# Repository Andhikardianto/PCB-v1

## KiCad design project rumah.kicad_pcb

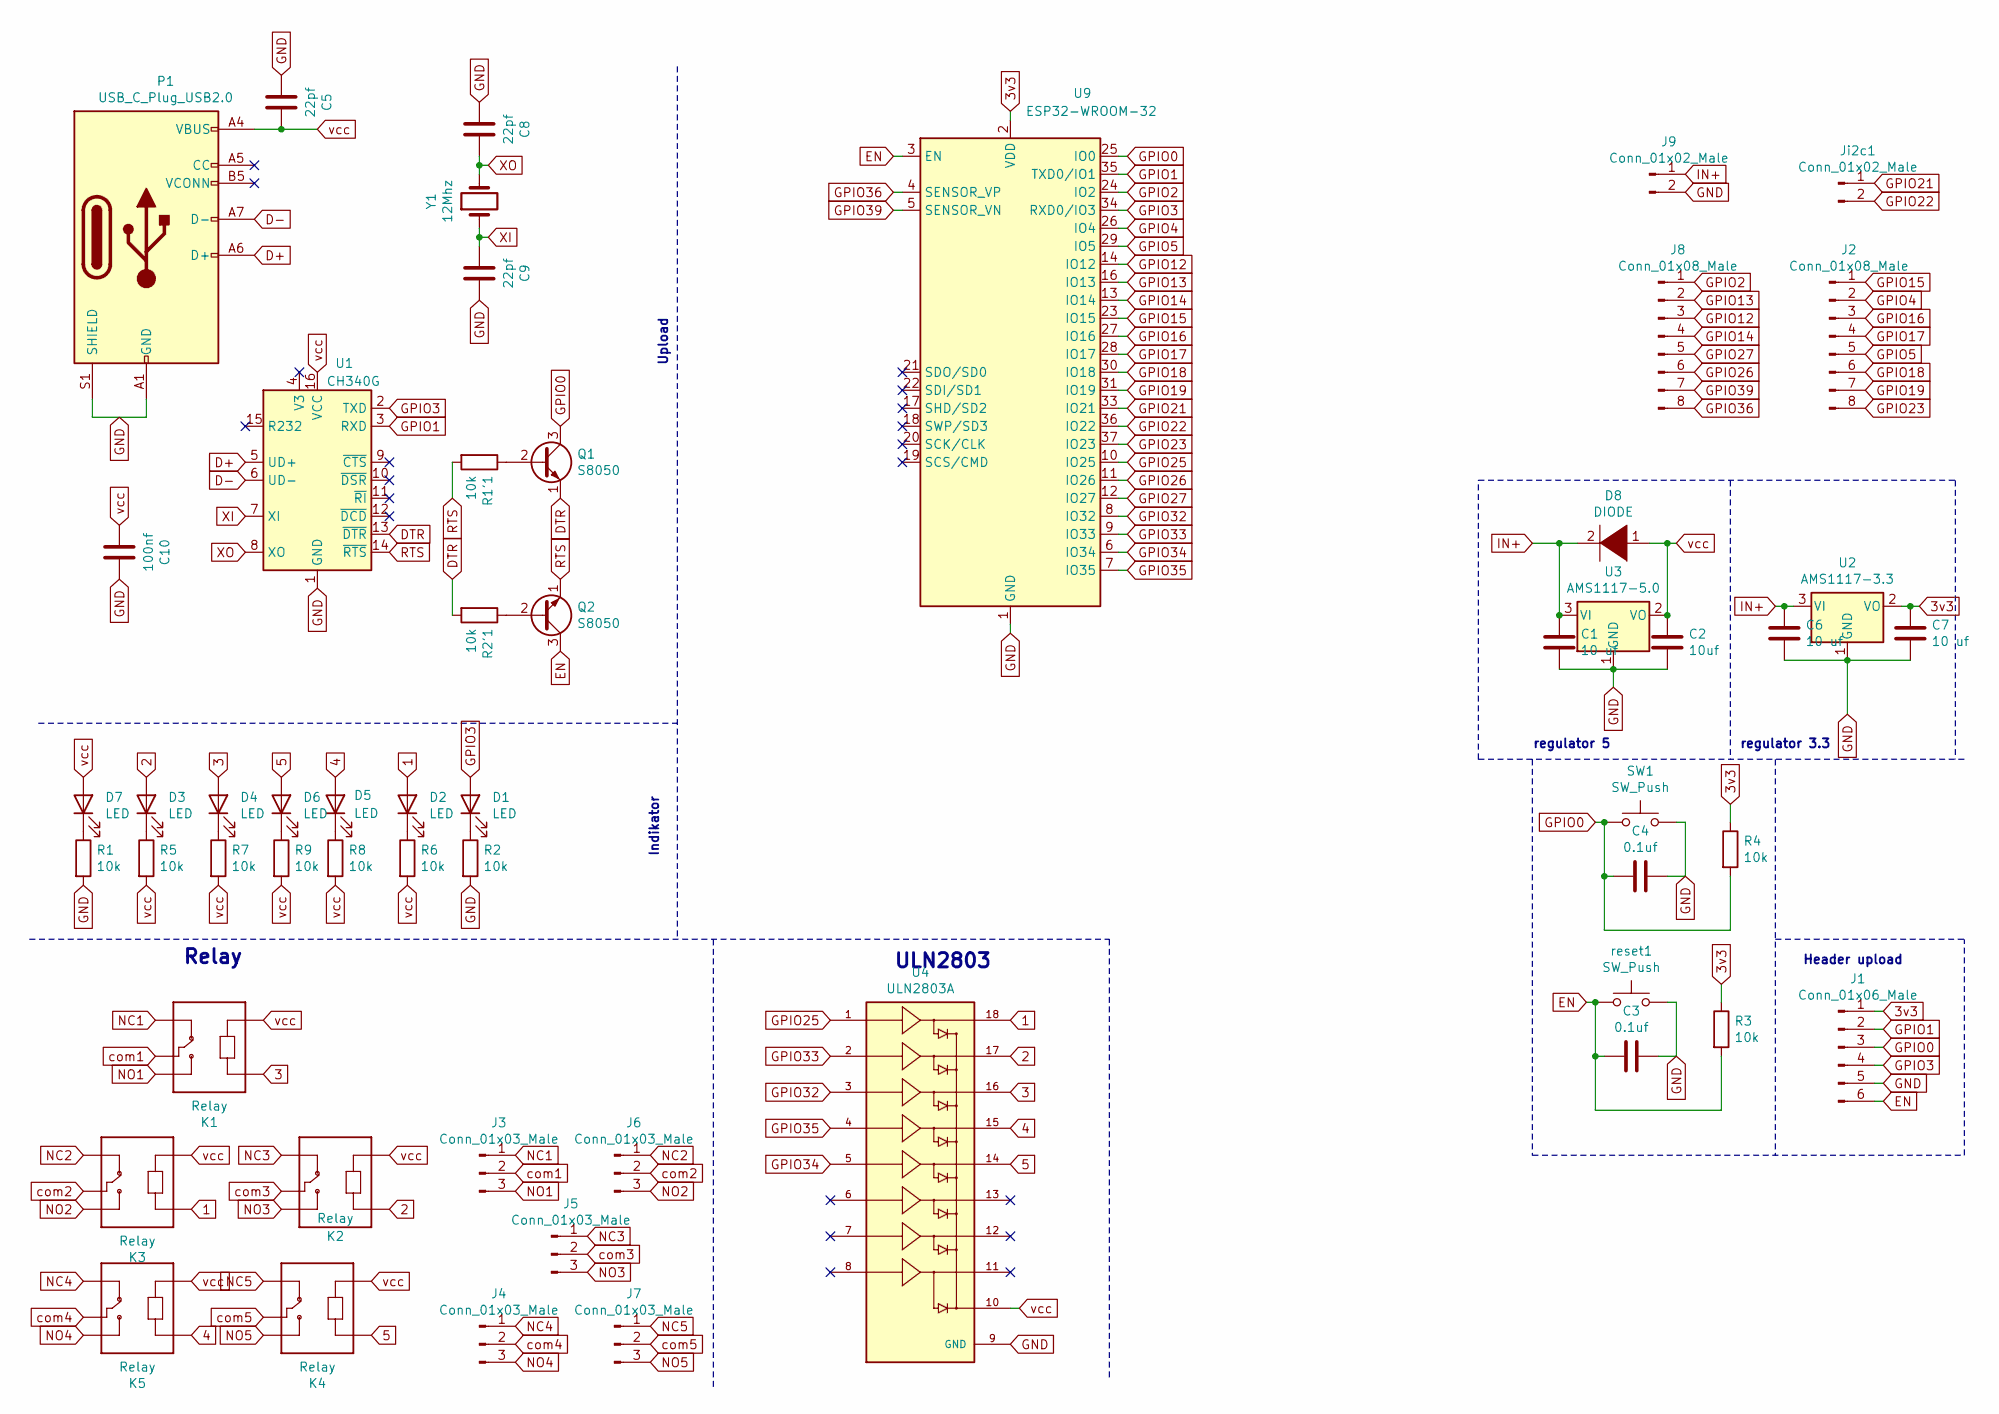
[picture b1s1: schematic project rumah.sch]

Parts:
C1, C6, C7: 10 uf; C_0805_2012Metric_Pad1.18x1.45mm_HandSolder
C2: 10uf; C_0805_2012Metric_Pad1.18x1.45mm_HandSolder
C3, C4: 0.1uf; C_0805_2012Metric_Pad1.18x1.45mm_HandSolder
C5, C8, C9: 22pf; C_0805_2012Metric_Pad1.18x1.45mm_HandSolder
C10: 100nf; C_0805_2012Metric_Pad1.18x1.45mm_HandSolder
D1, D2, D3, D4, D5, D6, D7: LED; LED_D5.0mm
D8: DIODE; D_SMA_Handsoldering
J1: Conn_01x06_Male; PinSocket_2x03_P2.54mm_Vertical
J2, J8: Conn_01x08_Male; PinHeader_1x08_P2.54mm_Vertical
J3, J4, J5, J6, J7: Conn_01x03_Male; TerminalBlock_Altech_AK300-3_P5.00mm
J9: Conn_01x02_Male; TerminalBlock_Altech_AK300-2_P5.00mm
Ji2c1: Conn_01x02_Male; PinHeader_1x02_P2.54mm_Vertical
K1, K2, K3, K4, K5: Relay; RELAY_SRD-05VDC-SL-C
P1: USB_C_Plug_USB2.0; USB_C_Receptacle_XKB_U262-16XN-4BVC11
Q1, Q2: S8050; TO-92_Inline
R1, R1'1, R2, R2'1, R3, R4, R5, R6, R7, R8, R9: 10k; R_0805_2012Metric_Pad1.20x1.40mm_HandSolder
SW1: SW_Push; SW_PUSH_6mm
U1: CH340G; SOIC-16_3.9x9.9mm_P1.27mm
U2: AMS1117-3.3; SOT-223-3_TabPin2
U3: AMS1117-5.0; SOT-223-3_TabPin2
U4: ULN2803A; DIP850W46P254L2324H393Q18; PARTREV 4
U9: ESP32-WROOM-32
Y1: 12Mhz; Crystal_HC51-U_Vertical
reset1: SW_Push; SW_PUSH_6mm

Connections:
1: D2.2 (A), K3.A1, U4.18
2: D3.2 (A), K2.A1, U4.17
3: D4.2 (A), K1.A1, U4.16
3v3: C7.1, J1.1, R3.1, R4.1, U2.2 (VO), U9.2 (VDD)
4: D5.2 (A), K5.A1, U4.15
5: D6.2 (A), K4.A1, U4.14
D+: P1.A6 (D+), U1.5 (UD+)
D-: P1.A7 (D-), U1.6 (UD-)
DTR: Q1.1 (E), R2'1.2, U1.13 (~DTR)
EN: C3.2, J1.6, Q2.3 (C), R3.2, U9.3 (EN), reset1.1
GND: C1.2, C2.2, C3.1, C4.1, C5.2, C6.2, C7.2, C8.2, C9.1, C10.1, J1.5, J9.2, P1.A1 (GND), P1.A12 (GND), P1.B1 (GND), P1.B12 (GND), P1.S1 (SHIELD), R1.2, R2.2, SW1.2, U1.1 (GND), U2.1 (GND), U3.1 (GND), U4.9 (GND), U9.1 (GND), U9.15 (GND), U9.38 (GND), U9.39 (GND), reset1.2
GPIO0: C4.2, J1.3, Q1.3 (C), R4.2, SW1.1, U9.25 (IO0)
GPIO1: J1.2, U1.3 (RXD), U9.35 (TXD0/IO1)
GPIO2: J8.1, U9.24 (IO2)
GPIO3: D1.2 (A), J1.4, U1.2 (TXD), U9.34 (RXD0/IO3)
GPIO4: J2.2, U9.26 (IO4)
GPIO5: J2.5, U9.29 (IO5)
GPIO12: J8.3, U9.14 (IO12)
GPIO13: J8.2, U9.16 (IO13)
GPIO14: J8.4, U9.13 (IO14)
GPIO15: J2.1, U9.23 (IO15)
GPIO16: J2.3, U9.27 (IO16)
GPIO17: J2.4, U9.28 (IO17)
GPIO18: J2.6, U9.30 (IO18)
GPIO19: J2.7, U9.31 (IO19)
GPIO21: Ji2c1.1, U9.33 (IO21)
GPIO22: Ji2c1.2, U9.36 (IO22)
GPIO23: J2.8, U9.37 (IO23)
GPIO25: U4.1, U9.10 (IO25)
GPIO26: J8.6, U9.11 (IO26)
GPIO27: J8.5, U9.12 (IO27)
GPIO32: U4.3, U9.8 (IO32)
GPIO33: U4.2, U9.9 (IO33)
GPIO34: U4.5, U9.6 (IO34)
GPIO35: U4.4, U9.7 (IO35)
GPIO36: J8.8, U9.4 (SENSOR_VP)
GPIO39: J8.7, U9.5 (SENSOR_VN)
IN+: C1.1, C6.1, D8.2 (A), J9.1, U2.3 (VI), U3.3 (VI)
NC1: J3.1, K1.NC
NC2: J6.1, K3.NC
NC3: J5.1, K2.NC
NC4: J4.1, K5.NC
NC5: J7.1, K4.NC
NO1: J3.3, K1.NO
NO2: J6.3, K3.NO
NO3: J5.3, K2.NO
NO4: J4.3, K5.NO
NO5: J7.3, K4.NO
unnamed: D1.1 (K), R2.1
unnamed: D2.1 (K), R6.1
unnamed: D3.1 (K), R5.1
unnamed: D4.1 (K), R7.1
unnamed: D5.1 (K), R8.1
unnamed: D6.1 (K), R9.1
unnamed: D7.1 (K), R1.1
unnamed: Q1.2 (B), R1'1.1
unnamed: Q2.2 (B), R2'1.1
RTS: Q2.1 (E), R1'1.2, U1.14 (~RTS)
XI: C9.2, U1.7 (XI), Y1.1
XO: C8.1, U1.8 (XO), Y1.2
com1: J3.2, K1.COM
com2: J6.2, K3.COM
com3: J5.2, K2.COM
com4: J4.2, K5.COM
com5: J7.2, K4.COM
vcc: C2.1, C5.1, C10.2, D7.2 (A), D8.1 (K), K1.A2, K2.A2, K3.A2, K4.A2, K5.A2, P1.A4 (VBUS), P1.A9 (VBUS), P1.B4 (VBUS), P1.B9 (VBUS), R5.2, R6.2, R7.2, R8.2, R9.2, U1.16 (VCC), U3.2 (VO), U4.10

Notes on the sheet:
regulator 3.3
regulator 5
Relay
ULN2803
Indikator
Upload
Header upload

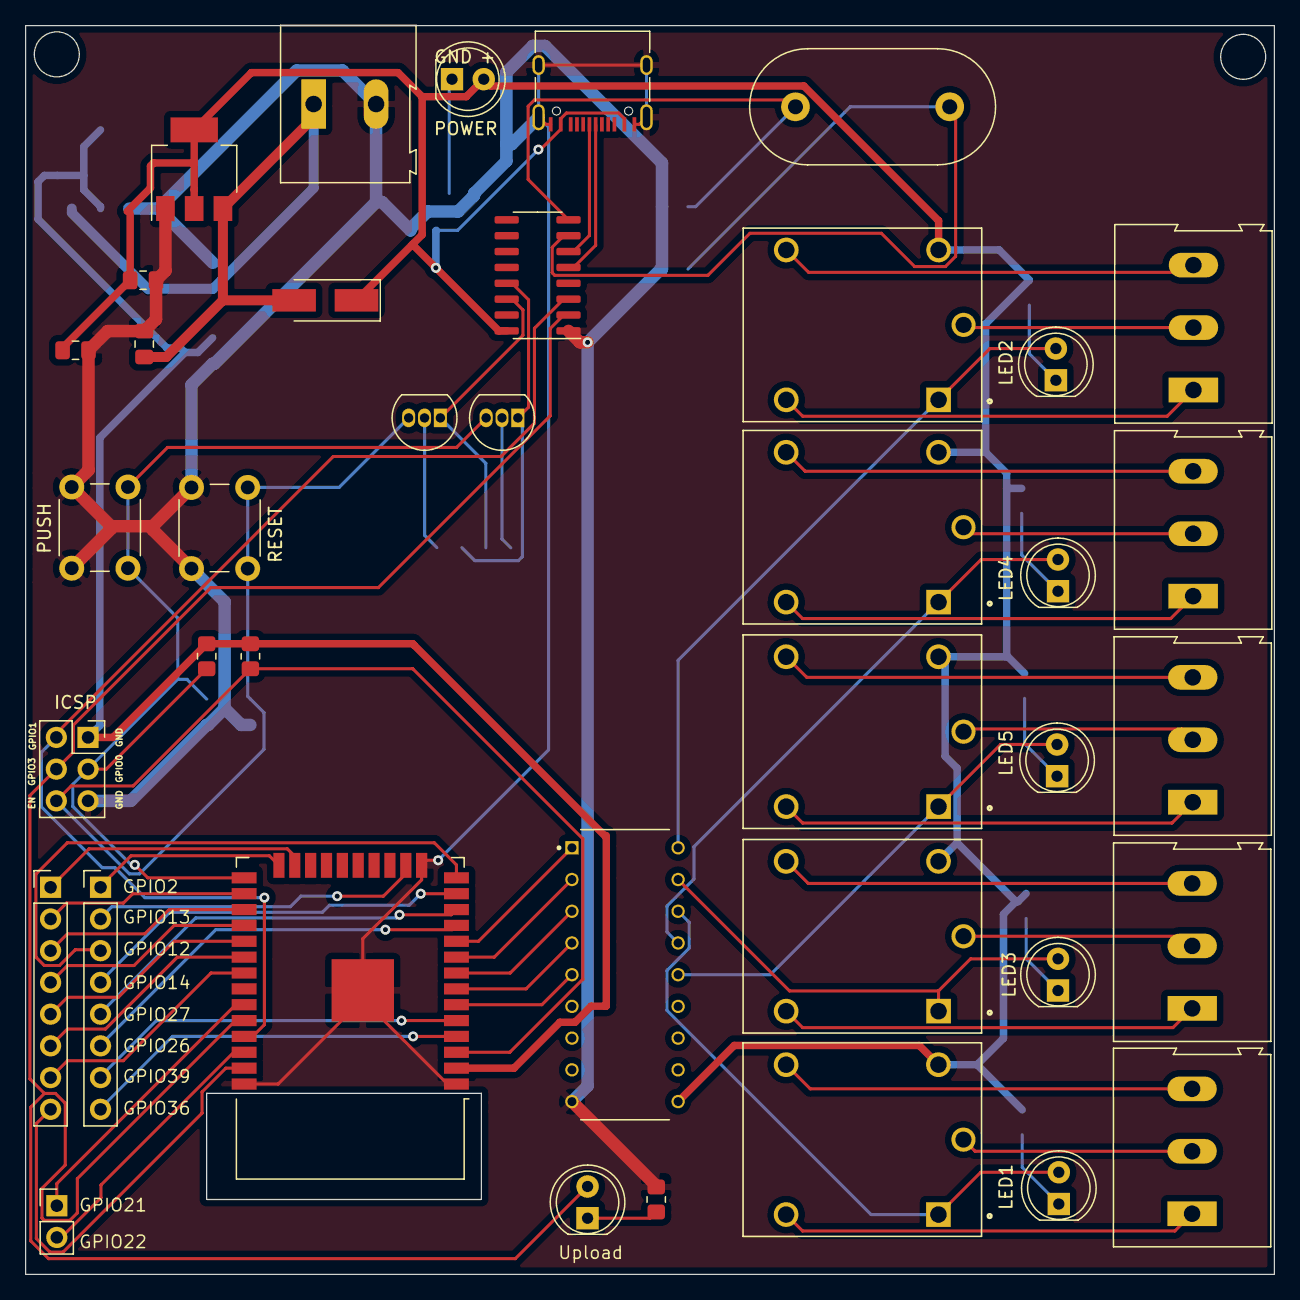
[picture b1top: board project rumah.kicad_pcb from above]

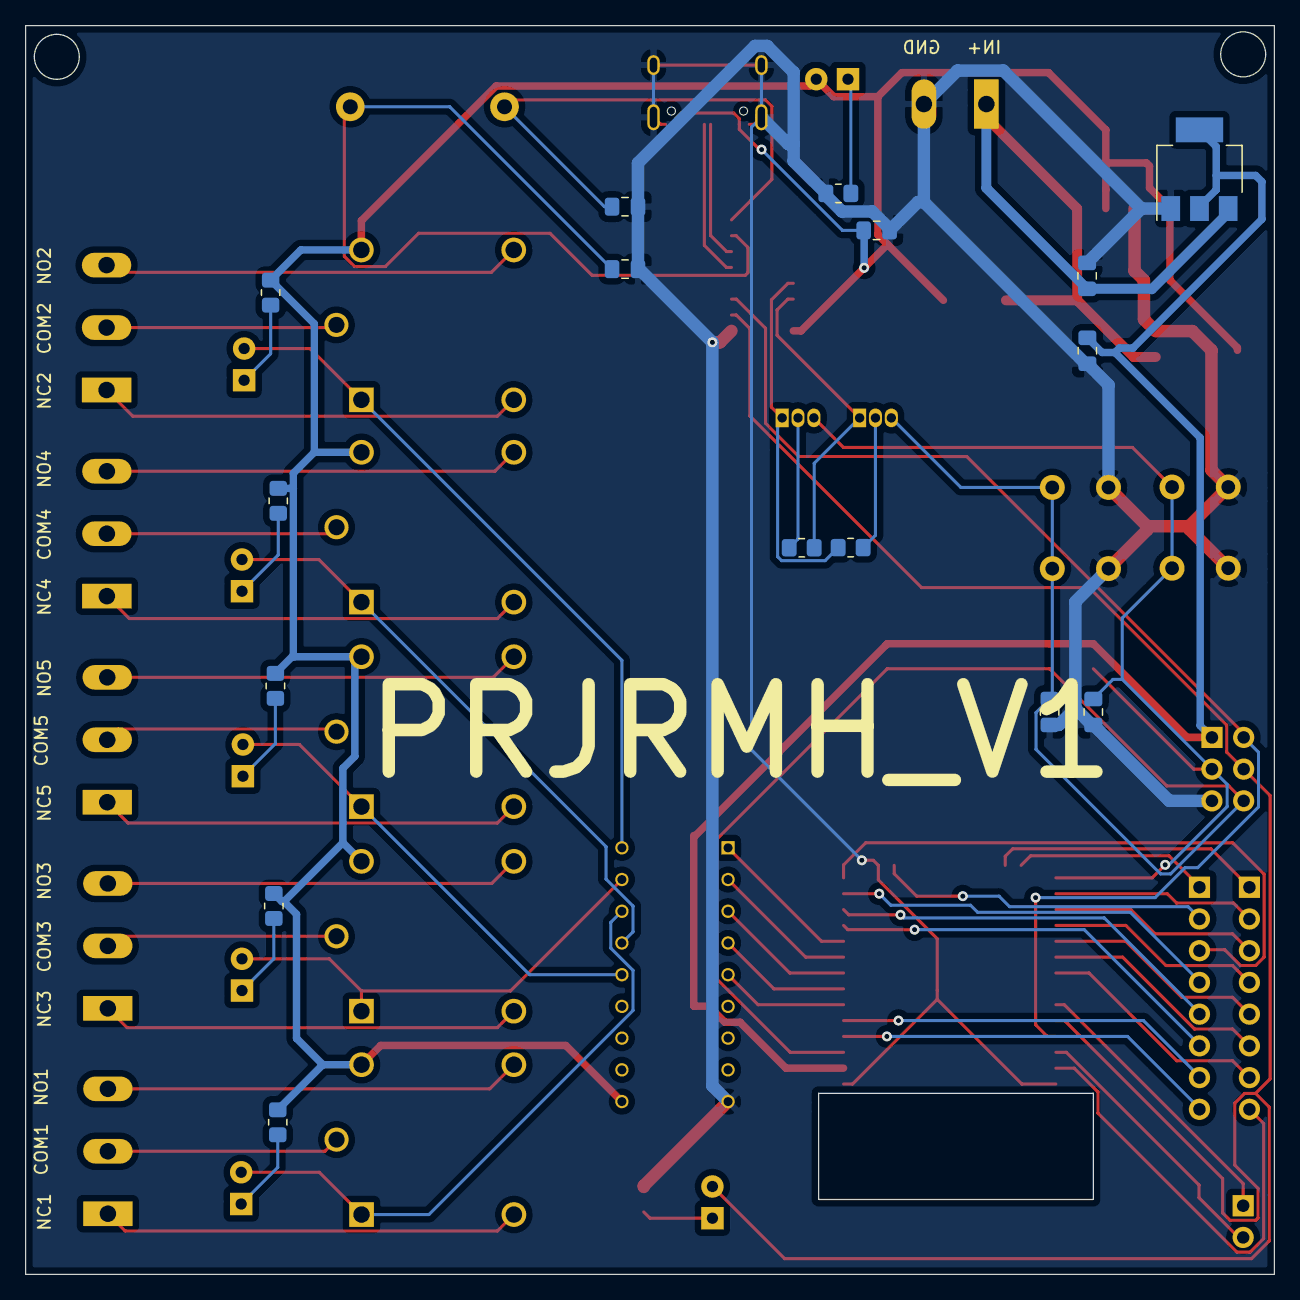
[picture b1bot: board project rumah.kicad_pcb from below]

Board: 2 copper layers, 100.0 x 100.0 mm, 55 parts (16 on the bottom side), 66 nets.
